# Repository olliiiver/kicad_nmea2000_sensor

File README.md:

# NMEA 2000 KiCAD PCB and sketch for analog inputs (e.g. water level, fuel gauge, switch, etc ...)

Based on https://github.com/ttlappalainen/NMEA2000

Can be used to create a NMEA 2000 device like a sensor for fuel gauges. The board is easy to work with since it contains ISP and serial ports. 

*Use at your own risk. Don't forget the right external fuses, etc.* 

## Prerequisites

- A NMEA2000 or Seatalk NG network
- PlatformIO CLI from https://platformio.org
- A PCB manufacturer of your choice and some SMD soldering experience 

## How to

### PCB

Equip SMD parts for power (LDO, etc) first and measure input to output voltage carefully. Adjust R4 (and R3) resistors, if necessary. If voltage is around 4.8V - 5V, place other parts. 

### Burn bootloader

0. Disconnect PCB from other power sources or adapters.
1. Connect an AVR ISP programmer (usbasp) to ISP port
2. Change into arduino-blink directory and type ```pio run --target fuses```. If the chip doesn't answer run avrdude manually with ```-B``` flag to set the bit clock rate, see  https://electronics.stackexchange.com/questions/388324/avrdude-error-program-enable-target-doesnt-answer-1
3. Change into arduino-blink directory and type ```pio run --target bootloader```
4. Optional: The sketch can be uploaded via ISP directly from arduino-sensor directory (```pio run --target program```)

### Upload sketch

0. Disconnect PCB from other power sources or adapters.
1. Connect an USB serial adapter to serial port
2. Change into arduino-sensor directory
3. Run ```pio run --target upload```

If errors appear during upload (e.g. ```programmer is out of sync``` or ```protocol error``` use another USB cable, USB hub or USB adapter. Check USB voltage (>4.89V) and ripple noise.

## BOM

- Case: RND 455-00182 
  https://www.reichelt.de/kunststoffgehaeuse-115-x-65-x-40-mm-ip65-rnd-455-00182-p193396.html
  https://www.distrelec.de/Web/Downloads/_t/ds/RND_455-00182_30064403_mcd_eng_tds.pdf

- AVR: AT90CAN128
  https://www.reichelt.de/atmel-ic-at-90can128-p55544.html

- Transceiver: MCP 2562-E/SN
  https://www.reichelt.de/bus-controller-1-treiber-1-empfaenger-so-8-mcp-2562-e-sn-p143745.html

- Connector: M12 Plug
  https://www.reichelt.de/sal-m12x1-5-pol-einbaustecker-sal12-fs50-p136981.html?&trstct=pol_38&nbc=1

- 12V to 5V: LDO 
 https://cdn-reichelt.de/documents/datenblatt/A200/LT3010EMS8E5.pdf

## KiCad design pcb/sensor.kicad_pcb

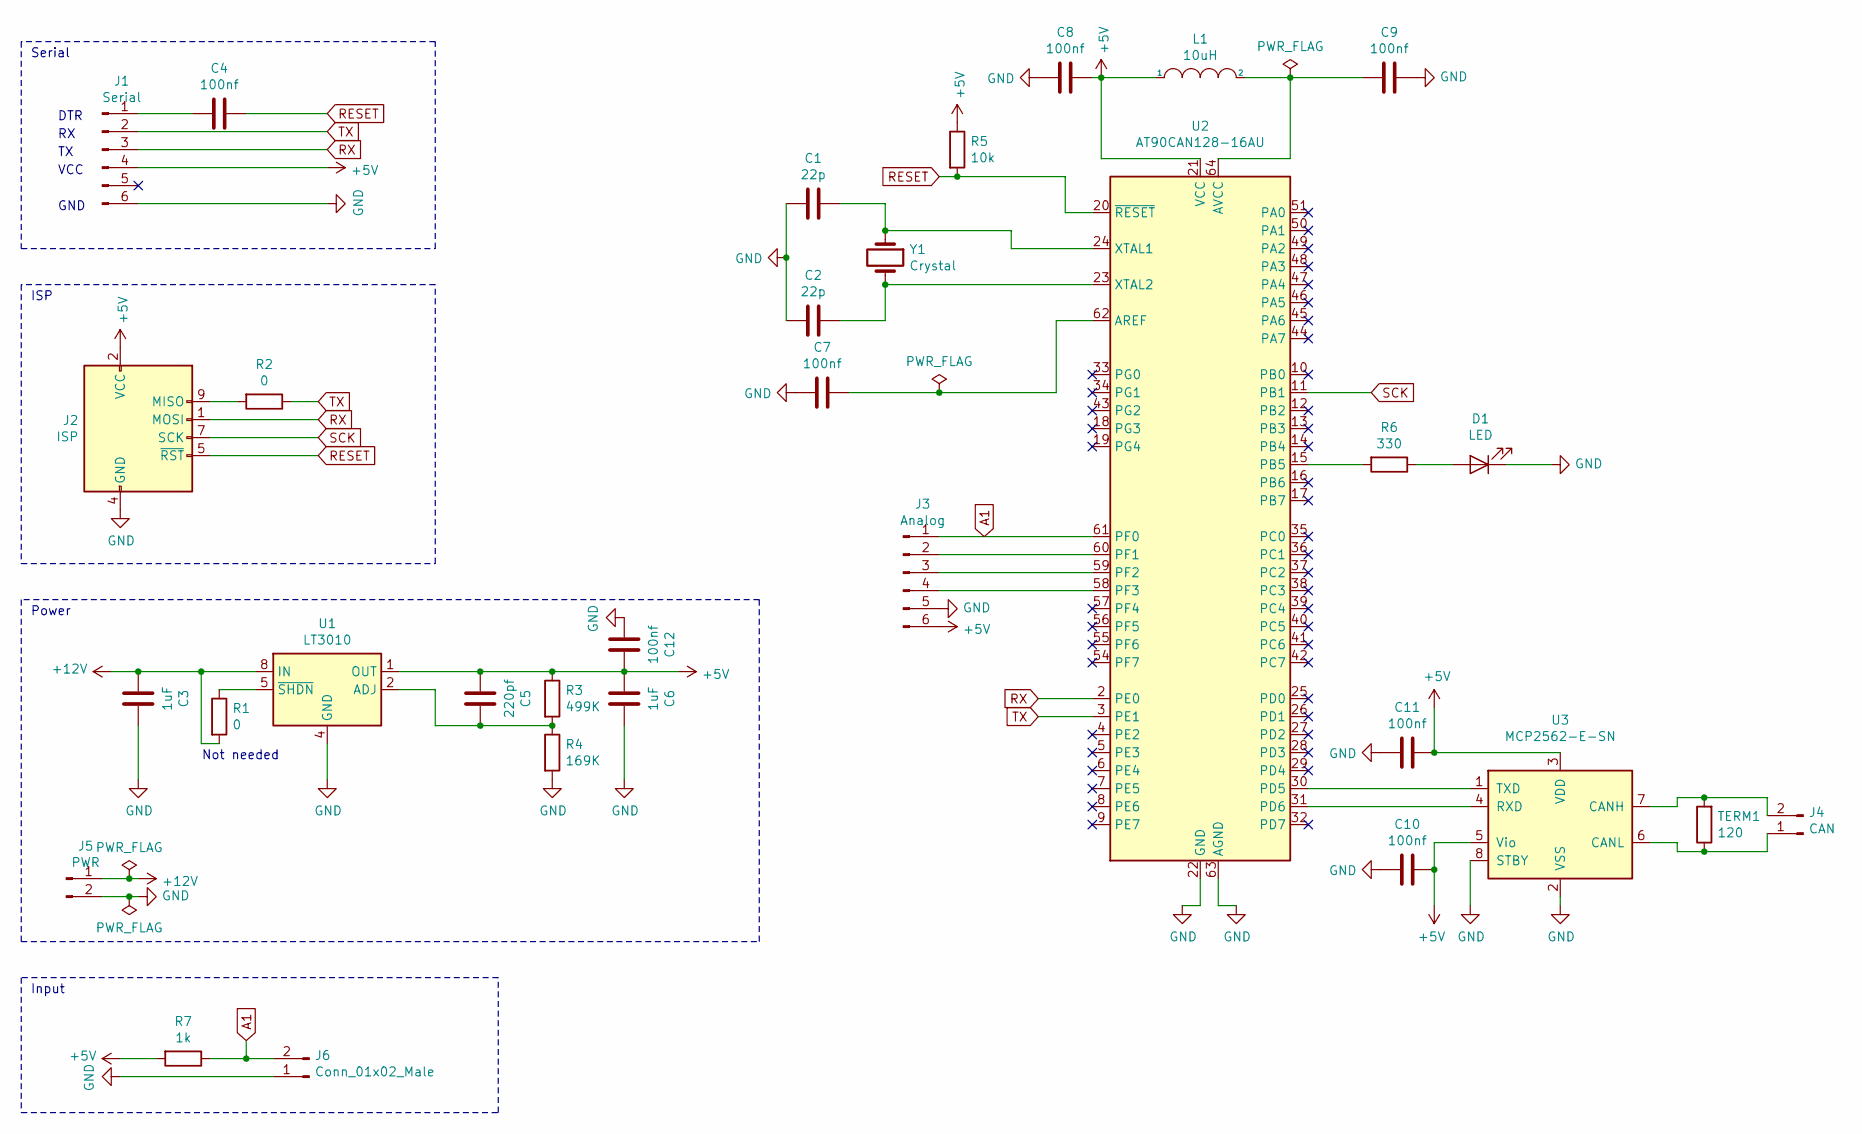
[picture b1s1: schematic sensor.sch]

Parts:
C1, C2: 22p; C_0805_2012Metric_Pad1.15x1.40mm_HandSolder
C3, C6: 1uF; C_0805_2012Metric_Pad1.15x1.40mm_HandSolder
C4, C7, C8, C9, C10, C11, C12: 100nf; C_0805_2012Metric_Pad1.15x1.40mm_HandSolder
C5: 220pf; C_0805_2012Metric_Pad1.15x1.40mm_HandSolder
D1: LED; LED_0805_2012Metric_Pad1.15x1.40mm_HandSolder
J1: Serial; PinHeader_1x06_P2.54mm_Vertical
J2: ISP; PinHeader_2x05_P2.54mm_Vertical
J3: Analog; PinHeader_1x06_P2.54mm_Vertical
J4: CAN; PinHeader_1x02_P2.54mm_Vertical
J5: PWR; PinHeader_1x02_P2.54mm_Vertical
J6: Conn_01x02_Male; PinHeader_1x02_P2.54mm_Vertical
L1: 10uH; L_0805_2012Metric_Pad1.15x1.40mm_HandSolder
R1, R2: 0; R_0805_2012Metric_Pad1.15x1.40mm_HandSolder
R3: 499K; R_0805_2012Metric_Pad1.15x1.40mm_HandSolder
R4: 169K; R_0805_2012Metric_Pad1.15x1.40mm_HandSolder
R5: 10k; R_0805_2012Metric_Pad1.15x1.40mm_HandSolder
R6: 330; R_0805_2012Metric_Pad1.15x1.40mm_HandSolder
R7: 1k; R_0805_2012Metric_Pad1.15x1.40mm_HandSolder
TERM1: 120; R_0805_2012Metric_Pad1.15x1.40mm_HandSolder
U1: LT3010; MSOP-8-1EP_3x3mm_P0.65mm_EP1.68x1.88mm
U2: AT90CAN128-16AU; TQFP-64_14x14mm_P0.8mm
U3: MCP2562-E-SN; SOIC-8_3.9x4.9mm_P1.27mm
Y1: Crystal; Crystal_HC49-4H_Vertical

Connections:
+5V: C5.2, C6.2, C8.1, C10.1, C11.1, C12.1, J1.4, J2.2 (VCC), J3.6, L1.1, R3.1, R5.1, R7.2, U1.1 (OUT), U2.21 (VCC), U2.52 (VCC), U3.3 (VDD), U3.5 (Vio)
+12V: C3.2, J5.1, R1.2, U1.8 (IN)
A1: J3.1, J6.2, R7.1, U2.61 (PF0)
GND: C1.2, C2.2, C3.1, C6.1, C7.2, C8.2, C9.1, C10.2, C11.2, C12.2, D1.1 (K), J1.6, J2.4 (GND), J2.6 (GND), J2.8 (GND), J2.10 (GND), J3.5, J5.2, J6.1, R4.2, U1.4 (GND), U1.9 (GND), U2.22 (GND), U2.53 (GND), U2.63 (AGND), U3.2 (VSS), U3.8 (STBY)
unnamed: C1.1, U2.24 (XTAL1), Y1.1
unnamed: C2.1, U2.23 (XTAL2), Y1.2
unnamed: C4.2, J1.1
unnamed: C5.1, R3.2, R4.1, U1.2 (ADJ)
unnamed: C7.1, U2.62 (AREF)
unnamed: C9.2, L1.2, U2.64 (AVCC)
unnamed: D1.2 (A), R6.1
unnamed: J2.9 (MISO), R2.2
unnamed: J3.2, U2.60 (PF1)
unnamed: J3.3, U2.59 (PF2)
unnamed: J3.4, U2.58 (PF3)
unnamed: J4.1, TERM1.1, U3.6 (CANL)
unnamed: J4.2, TERM1.2, U3.7 (CANH)
unnamed: R1.1, U1.5 (~SHDN)
unnamed: R6.2, U2.15 (PB5)
unnamed: U2.30 (PD5), U3.1 (TXD)
unnamed: U2.31 (PD6), U3.4 (RXD)
RESET: C4.1, J2.5 (~RST), R5.2, U2.20 (~RESET)
RX: J1.3, J2.1 (MOSI), U2.2 (PE0)
SCK: J2.7 (SCK), U2.11 (PB1)
TX: J1.2, R2.1, U2.3 (PE1)

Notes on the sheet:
Serial
ISP
Power
Input
DTR
VCC
GND
Not needed

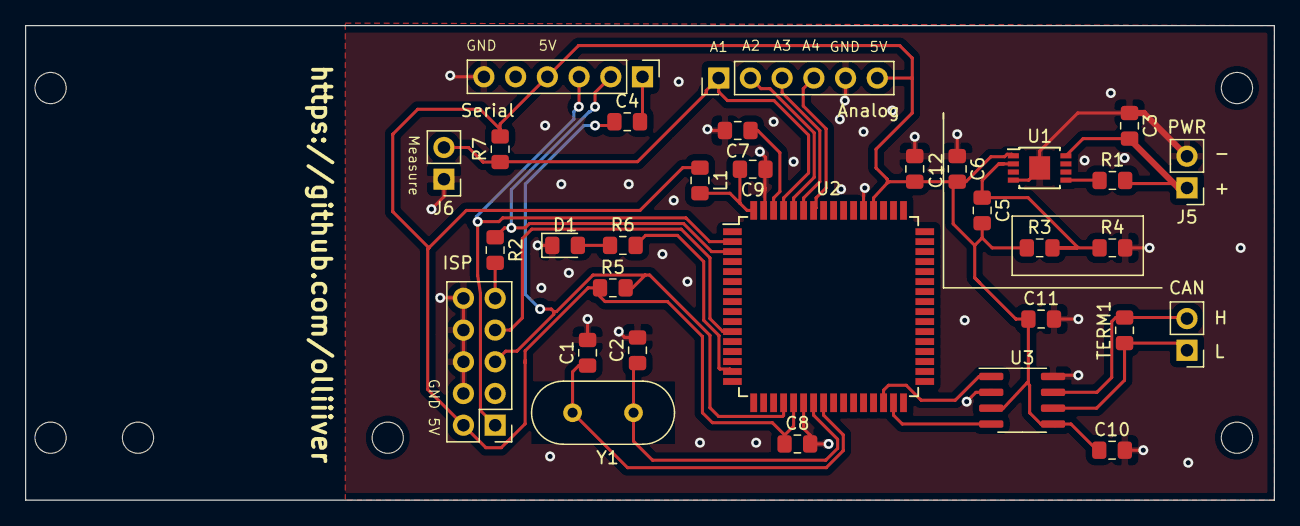
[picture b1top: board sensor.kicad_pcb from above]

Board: 2 copper layers, 100.0 x 38.0 mm, 32 parts (0 on the bottom side), 25 nets.

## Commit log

2020-05-10 first
2020-05-10 readme
2020-09-21 Fix buffer size which caused deadlock
